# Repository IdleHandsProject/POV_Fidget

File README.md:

# POV Arduino Fidget Spinner!

A lot of the info is in the video, check it out(Click the Image)!

Some more useful links:

https://hackaday.io/project/25538-pov-fidget-spinner

https://www.instructables.com/id/POV-Arduino-Fidget-Spinner/

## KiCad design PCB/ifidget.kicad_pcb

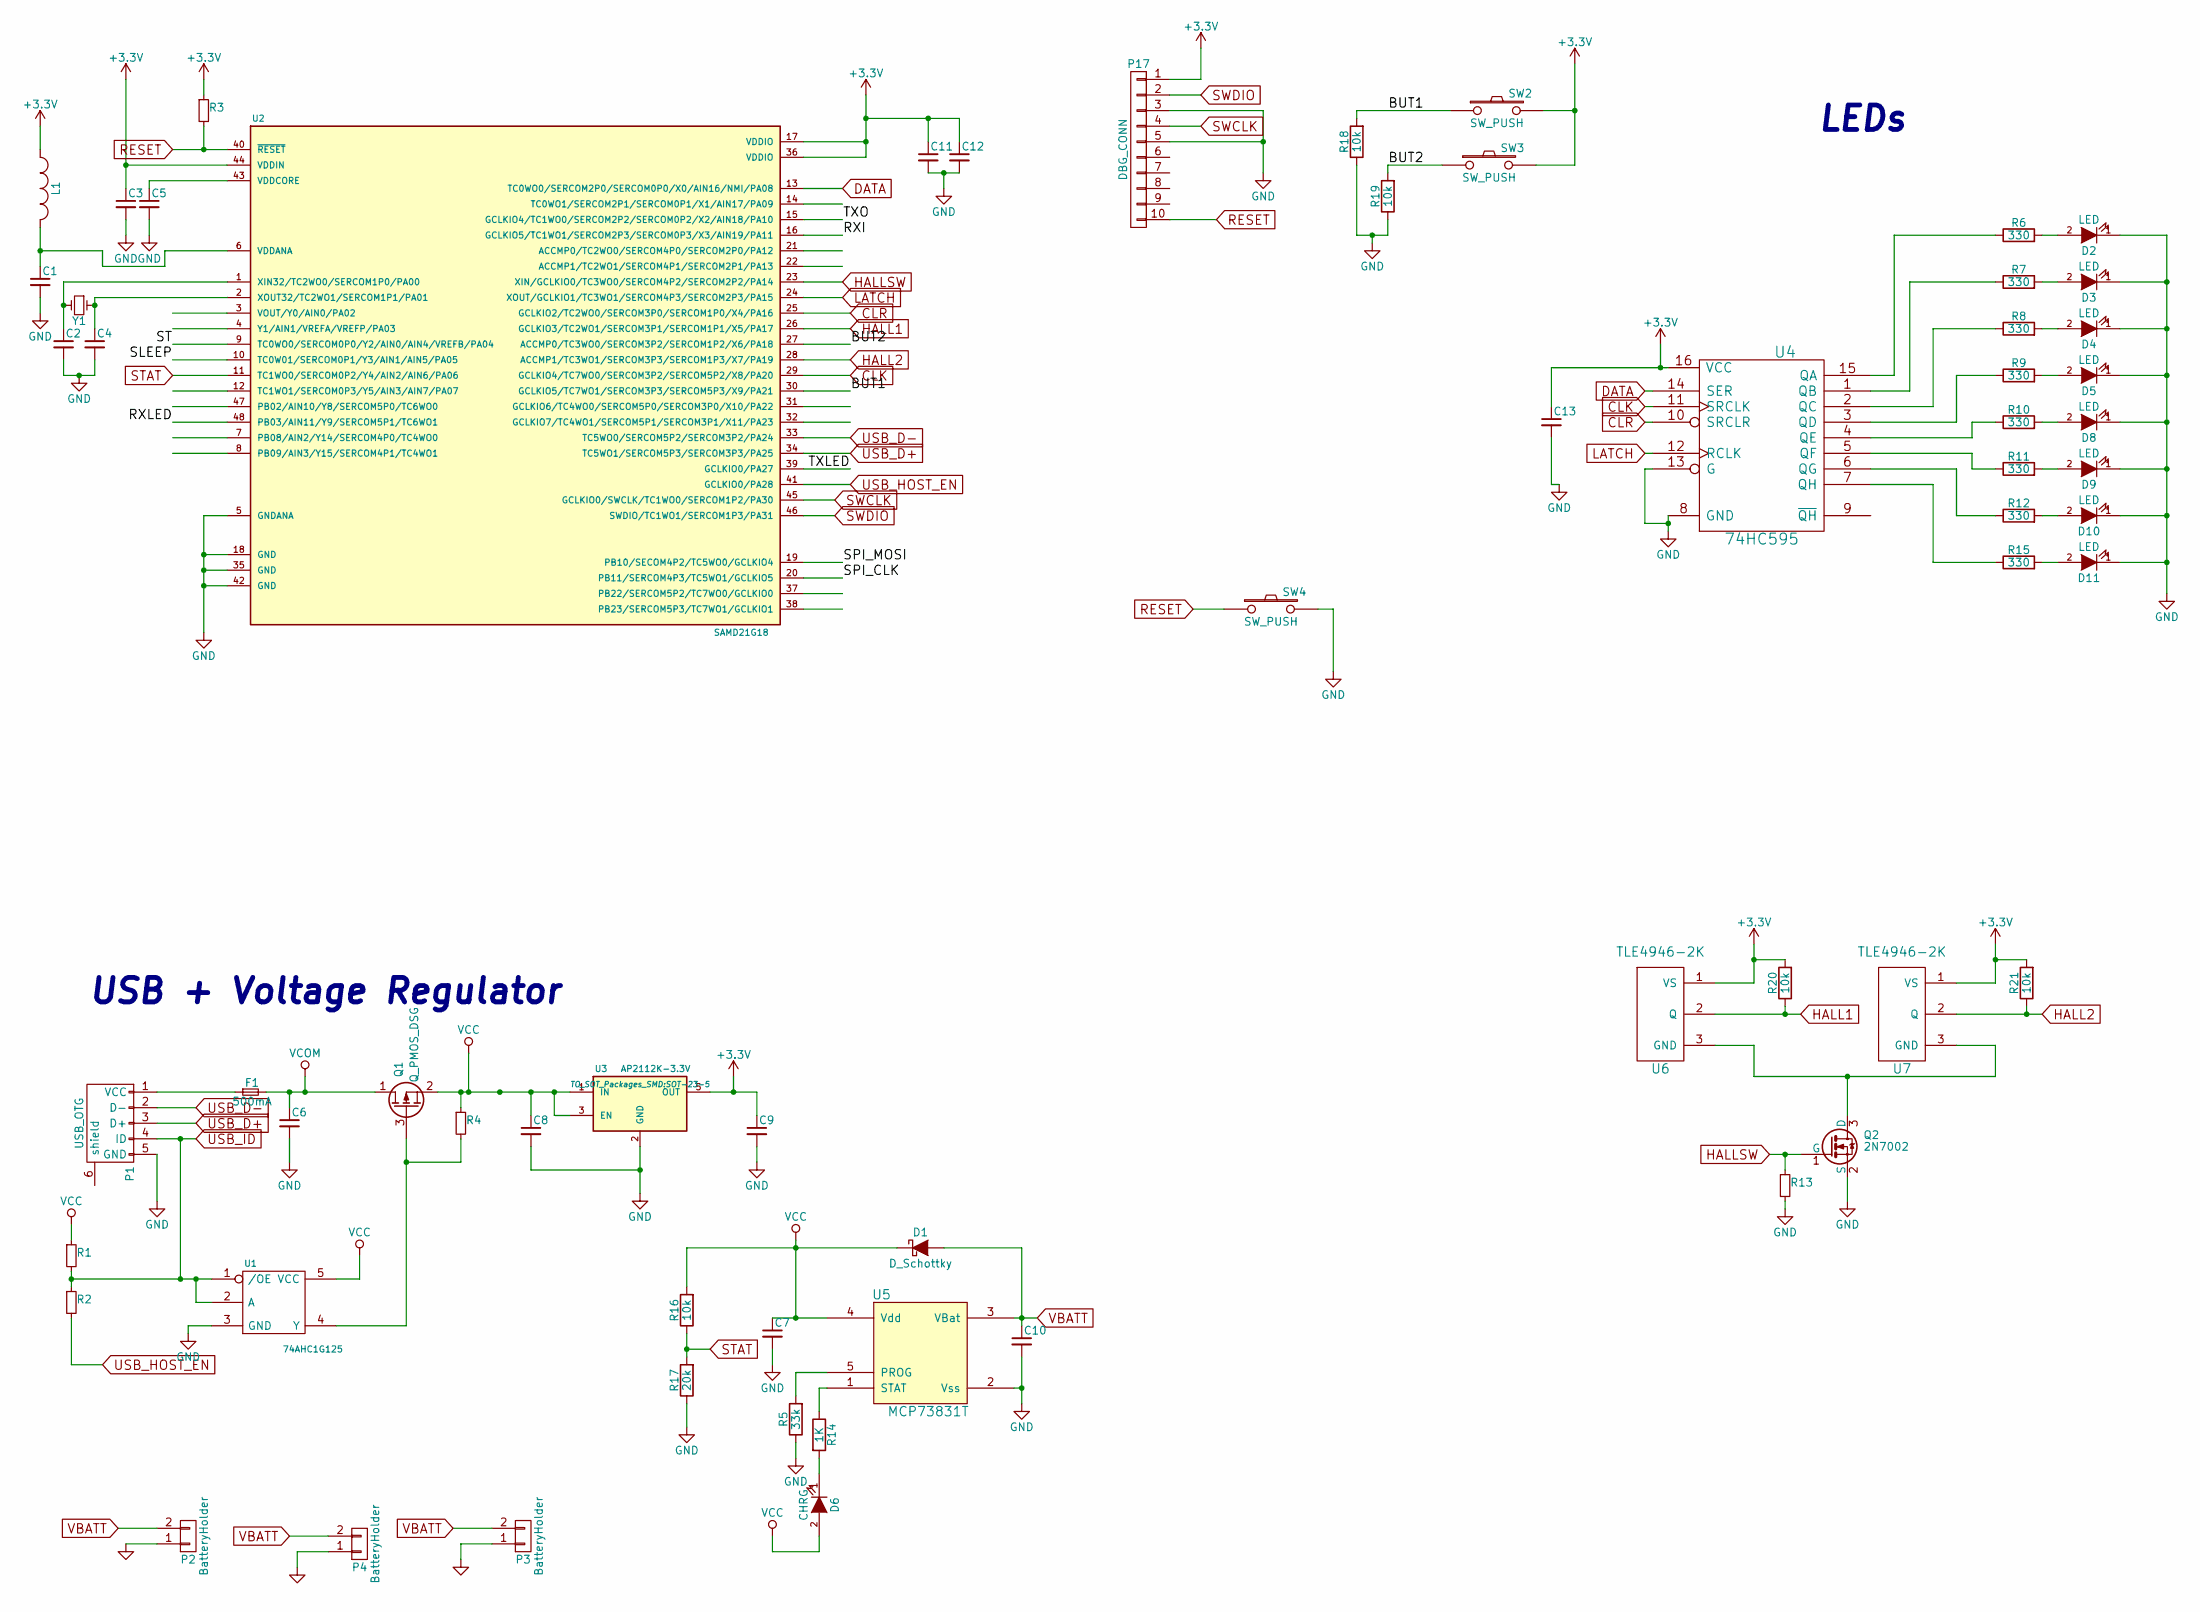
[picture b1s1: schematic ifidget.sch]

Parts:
C1, C3, C5, C11, C12: 0.1uF; C_0402_Hand; Digikey Part No. 490-6328-1-ND
C2, C4: 15pF; C_0402_Hand; Digikey Part No. 712-1261-1-ND
C6: 2.2uF; C_0402_Hand; Digikey Part No. 1276-1291-1-ND
C7, C10: 4.7uF; C_0402_Hand; Digikey Part No. 490-5915-1-ND
C8, C13: 1uF; C_0402_Hand; Digikey Part No. 490-4516-1-ND
C9: 2.2uF; C_0402_Hand; Digikey Part No. 1276-1469-1-ND
D1: D_Schottky; sod80c; Digikey Part No. 497-3381-1-ND
D2, D3, D4, D5, D8, D9, D10, D11: LED; Led_0603; Digikey Part No. 160-1436-1-ND
D6: CHRG; Led_0603; Digikey Part No. 160-1436-1-ND
F1: 500mA; c_1206; Digikey Part No. 507-1803-1-ND
L1: FB - 30Ohm; R_SM0603; Digikey Part No. 445-2986-1-ND
P1: USB_OTG; USB_Micro-B_VERT; Digikey Part No. WM9734CT-ND
P2, P3, P4: BatteryHolder; CoinCellHolder_TH; Digikey Part No. BK-912-G-CT-ND
P17: DBG_CONN; Pin_Header_Straight_2x05_Pitch1.27mm; Digikey Part No. 1175-1627-ND
Q1: Q_PMOS_DSG; SOT23; Digikey Part No. DMG2307L-7DICT-ND
Q2: 2N7002; SOT-23; Digikey Part No. 1727-4793-1-ND
R1, R13: 100k; R_0402_Hand; Digikey Part No. 311-100KLRCT-ND
R2, R6, R7, R8, R9, R10, R11, R12, R15: 330; R_0402_Hand; Digikey Part No. 311-330JRCT-ND
R3, R16, R18, R19, R20, R21: 10k; R_0402_Hand; Digikey Part No. 311-10KJRCT-ND
R4: 47K; R_0402_Hand; Digikey Part No. 311-47.0KLRCT-ND
R5: 33k; R_0402_Hand; Digikey Part No. 311-33KJRCT-ND
R14: 1K; R_0402_Hand; Digikey Part No. 311-1.0KJRCT-ND
R17: 20k; R_0402_Hand; Digikey Part No. 311-20KJRCT-ND
SW2, SW3: SW_PUSH; SW_SPST_PTS645; Digikey Part No. CKN9112CT-ND
SW4: SW_PUSH; SOLDER-JUMPER_1-WAY; Digikey Part No. CKN9084CT-ND
U1: 74AHC1G125; sot23-5; Digikey Part No. 1727-6024-1-ND
U2: SAMD21G18; TQFP-48_7x7mm_Pitch0.5mm; Digikey Part No. ATSAMD21G18A-AU-ND
U3: AP2112K-3.3V; SOT-23-5; Digikey Part No. AP2112K-3.3TRG1DICT-ND
U4: 74HC595; pvqfn-n16; Digikey Part No. 1727-3327-1-ND
U5: MCP73831T; sot23-5; Digikey Part No. MCP73831T-2ACI/OTCT-ND
U6, U7: TLE4946-2K; SOT23; Digikey Part No. TLE49462KHTSA1CT-ND
Y1: Crystal_Small; crystal_smd_5x3.2mm; Digikey Part No. XC1617CT-ND

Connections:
+3V3: C3.1, C9.1, C11.1, C12.1, C13.1, L1.1, P17.1, R3.1, R20.2, R21.2, SW2.2, SW3.2, U2.17 (VDDIO), U2.36 (VDDIO), U2.44 (VDDIN), U3.5 (OUT), U4.16 (VCC), U6.1 (VS), U7.1 (VS)
/BUT1: R18.2, SW2.1, U2.30 (GCLKIO5/TC7WO1/SERCOM3P3/SERCOM5P3/X9/P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)
/BUT2: R19.2, SW3.1, U2.27 (ACCMP0/TC3WO0/SERCOM3P2/SERCOM1P2/X6/PA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)
/RXI: U2.16 (GCLKIO5/TC1WO1/SERCOM2P3/SERCOM0P3/X3/A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)
/RXLED: U2.48 (PB03/AIN11/Y9/SERCOM5P1/TC6WO1)
/SLEEP: U2.10 (TC0W01/SERCOM0P1/Y3/AIN1/AIN5/PA05)
/SPI_CLK: U2.20 (PB11/SERCOM4P3/TC5WO1/GCLKIO5)
/SPI_MOSI: U2.19 (PB10/SECOM4P2/TC5WO0/GCLKIO4)
/ST: U2.9 (TC0WO0/SERCOM0P0/Y2/AIN0/AIN4/VREFB/PA04)
/TXLED: U2.39 (GCLKIO0/PA27)
/TXO: U2.15 (GCLKIO4/TC1WO0/SERCOM2P2/SERCOM0P2/X2/A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)
CLK: U2.29 (GCLKIO4/TC7WO0/SERCOM3P2/SERCOM5P2/X8/P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), U4.11 (SRCLK)
CLR: U2.25 (GCLKIO2/TC2WO0/SERCOM3P0/SERCOM1P0/X4/P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), U4.10 (SRCLR)
DATA: U2.13 (TC0WO0/SERCOM2P0/SERCOM0P0/X0/AIN16/NMI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), U4.14 (SER)
GND: C1.2, C2.2, C3.2, C4.2, C5.2, C6.2, C7.2, C8.2, C9.2, C10.2, C11.2, C12.2, C13.2, D2.1 (K), D3.1 (K), D4.1 (K), D5.1 (K), D8.1 (K), D9.1 (K), D10.1 (K), D11.1 (K), P1.5 (GND), P2.1, P3.1, P4.1, P17.3, P17.5, Q2.2 (S), R5.1, R13.2, R17.1, R18.1, R19.1, SW4.2, U1.3 (GND), U2.5 (GNDANA), U2.18 (GND), U2.35 (GND), U2.42 (GND), U3.2 (GND), U4.8 (GND), U4.13 (G), U5.2 (Vss); also elsewhere on the board
HALL1: R20.1, U2.26 (GCLKIO3/TC2WO1/SERCOM3P1/SERCOM1P1/X5/P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), U6.2 (Q); also elsewhere on the board
HALL2: R21.1, U2.28 (ACCMP1/TC3WO1/SERCOM3P3/SERCOM1P3/X7/PA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), U7.2 (Q); also elsewhere on the board
HALLSW: Q2.1 (G), R13.1, U2.23 (XIN/GCLKIO0/TC3WO0/SERCOM4P2/SERCOM2P2/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)
LATCH: U2.24 (XOUT/GCLKIO1/TC3WO1/SERCOM4P3/SERCOM2P3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), U4.12 (RCLK)
unnamed: C1.1, L1.2, U2.6 (VDDANA)
unnamed: C2.1, U2.1 (XIN32/TC2WO0/SERCOM1P0/PA00), Y1.2
unnamed: C4.1, U2.2 (XOUT32/TC2WO1/SERCOM1P1/PA01), Y1.1
unnamed: C5.1, U2.43 (VDDCORE)
unnamed: D2.2 (A), R6.2
unnamed: D3.2 (A), R7.2
unnamed: D4.2 (A), R8.2
unnamed: D5.2 (A), R9.2
unnamed: D6.1 (K), R14.2
unnamed: D8.2 (A), R10.2
unnamed: D9.2 (A), R11.2
unnamed: D10.2 (A), R12.2
unnamed: D11.2 (A), R15.2
unnamed: F1.1, P1.1 (VCC)
unnamed: Q1.3 (G), R4.2, U1.4 (Y)
unnamed: Q2.3 (D), U6.3 (GND), U7.3 (GND)
unnamed: R5.2, U5.5 (PROG)
unnamed: R6.1, U4.15 (QA)
unnamed: R7.1, U4.1 (QB)
unnamed: R8.1, U4.2 (QC)
unnamed: R9.1, U4.3 (QD)
unnamed: R10.1, U4.4 (QE)
unnamed: R11.1, U4.5 (QF)
unnamed: R12.1, U4.6 (QG)
unnamed: R14.1, U5.1 (STAT)
unnamed: R15.1, U4.7 (QH)
RESET: P17.10, R3.2, SW4.1, U2.40 (~RESET~)
STAT: R16.1, R17.2, U2.11 (TC1WO0/SERCOM0P2/Y4/AIN2/AIN6/PA06)
SWCLK: P17.4, U2.45 (GCLKIO0/SWCLK/TC1WO0/SERCOM1P2/PA30)
SWDIO: P17.2, U2.46 (SWDIO/TC1WO1/SERCOM1P3/PA31)
USB_D+: P1.3 (D+), U2.34 (TC5WO1/SERCOM5P3/SERCOM3P3/PA25)
USB_D-: P1.2 (D-), U2.33 (TC5WO0/SERCOM5P2/SERCOM3P2/PA24)
USB_HOST_EN: R2.2, U2.41 (GCLKIO0/PA28)
USB_ID: P1.4 (ID), R1.2, R2.1, U1.1 (/OE), U1.2 (A)
VBATT: C10.1, D1.2 (A), P2.2, P3.2, P4.2, U5.3 (VBat)
VCC: C7.1, C8.1, D1.1 (K), D6.2 (A), Q1.2 (S), R1.1, R4.1, R16.2, U1.5 (VCC), U3.1 (IN), U3.3 (EN), U5.4 (Vdd)
VCOM: C6.1, F1.2, Q1.1 (D)

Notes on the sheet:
USB + Voltage Regulator
LEDs

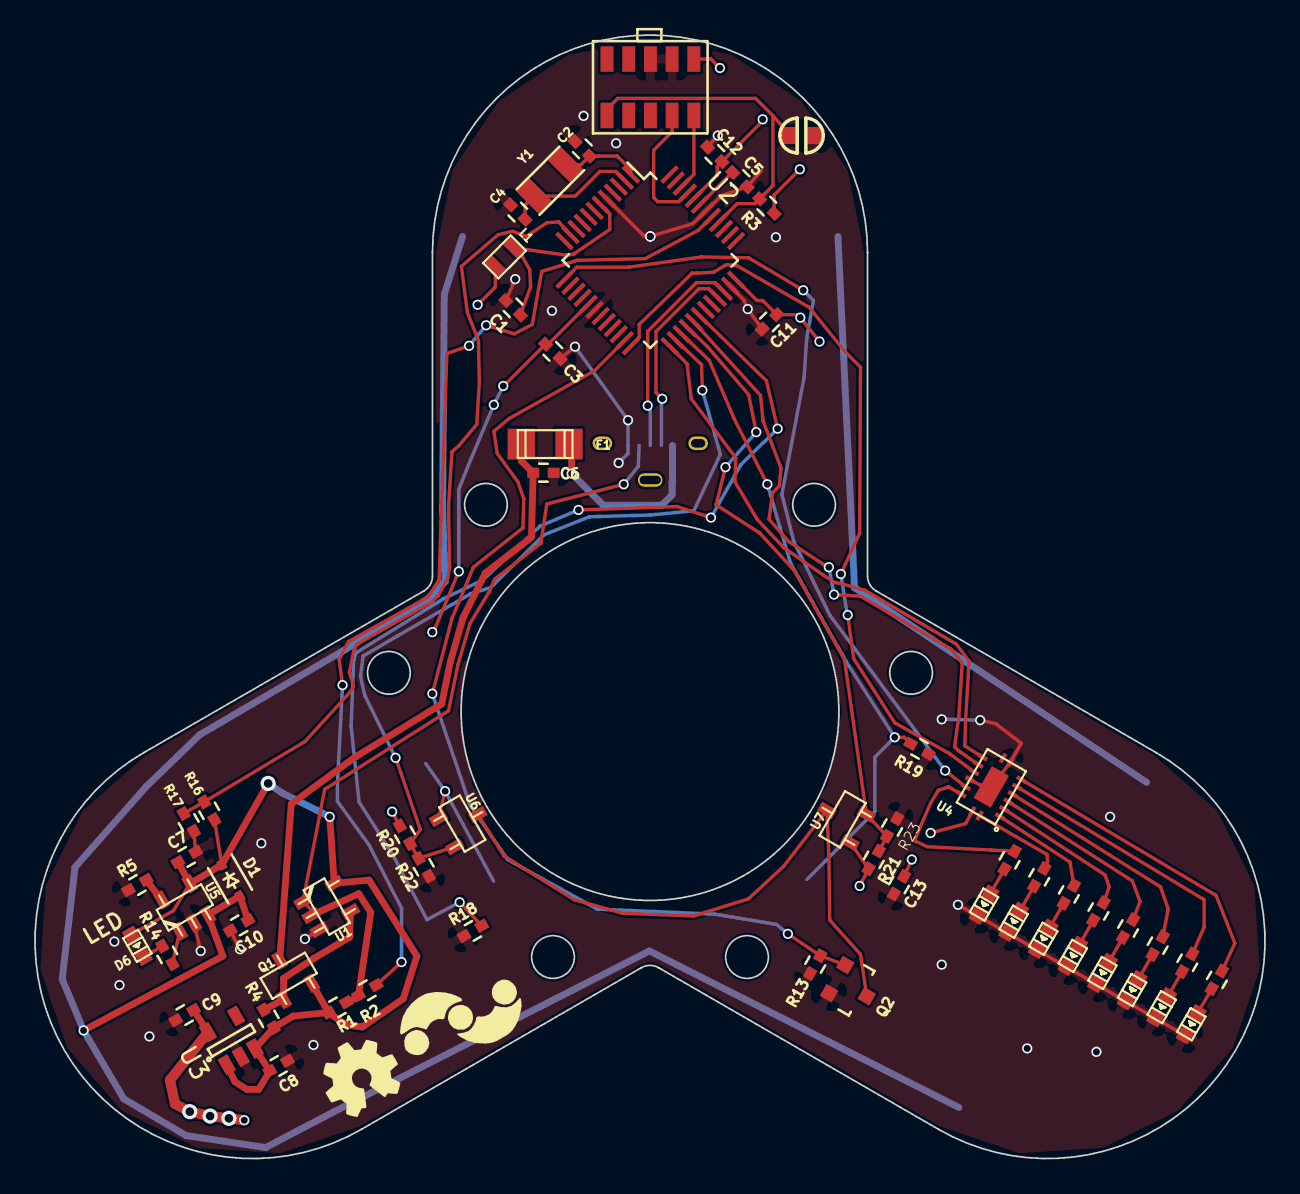
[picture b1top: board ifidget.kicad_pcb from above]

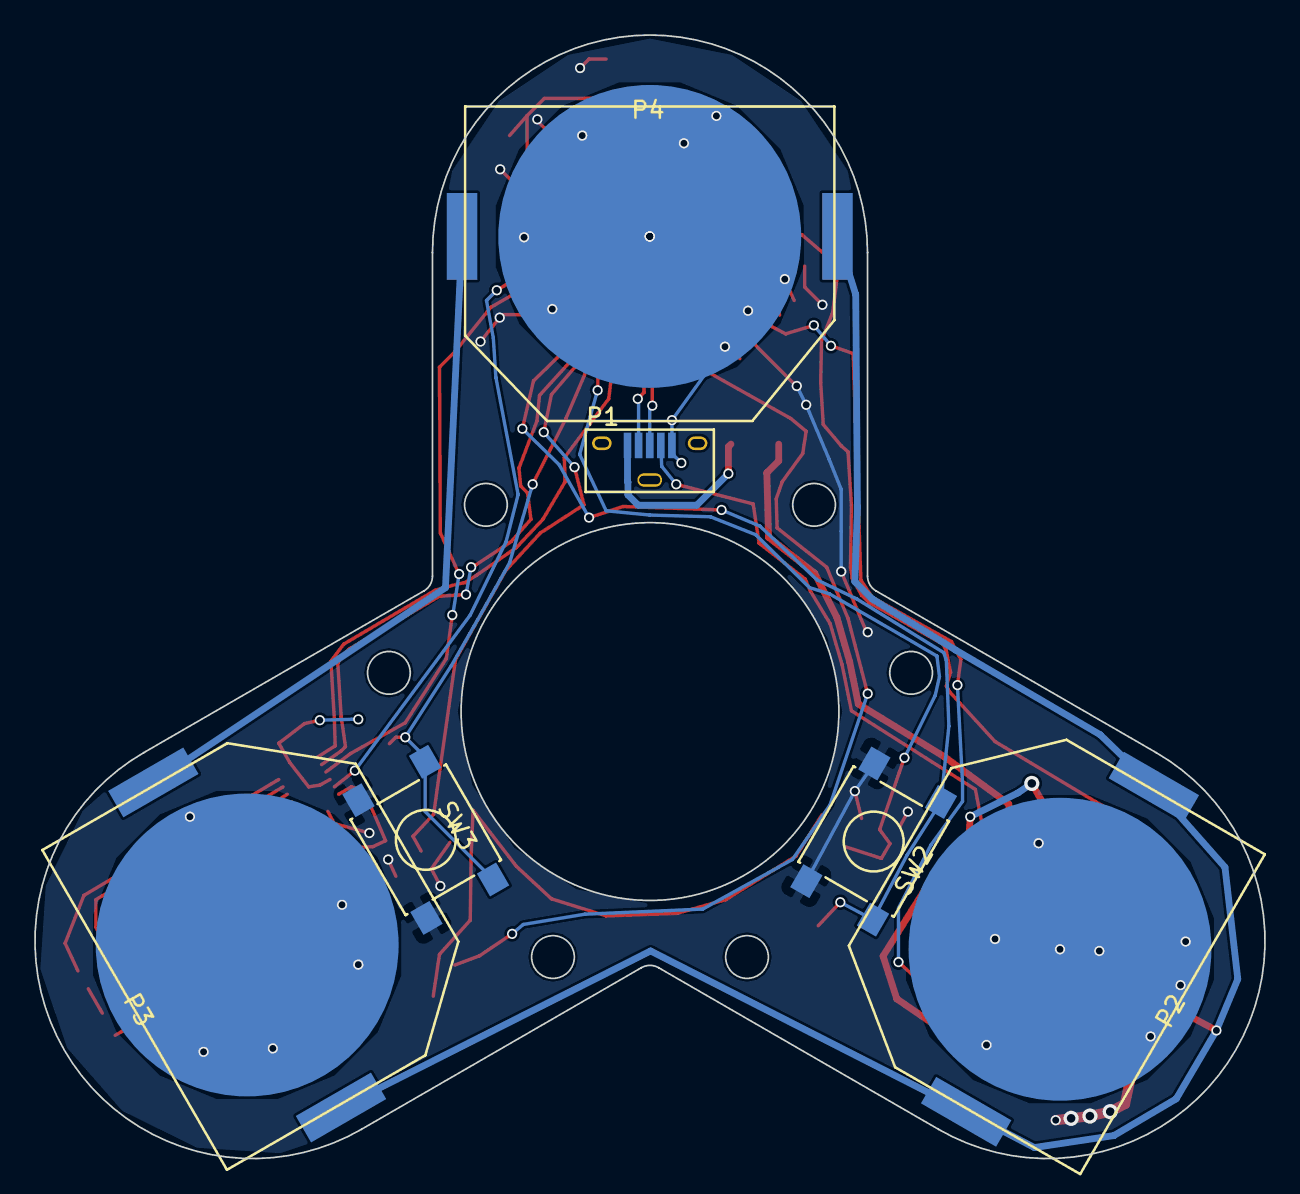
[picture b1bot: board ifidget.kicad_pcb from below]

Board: 2 copper layers, 71.9 x 65.7 mm, 66 parts (6 on the bottom side), 48 nets.

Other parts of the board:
R22, R23: 10k; R_0402_Hand

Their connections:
GND: R22.1, R23.1; also elsewhere on the board
HALL1: R22.2; also elsewhere on the board
HALL2: R23.2; also elsewhere on the board

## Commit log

2017-06-24 Removed some parts, added STLs
2017-06-24 fixed Q1 Pads
2017-06-24 Update .gitignore
    Added Windows.gitignore.
2017-06-25 updated firmware
2017-06-28 fixes to power and listed issues
2017-06-28 Small fix
